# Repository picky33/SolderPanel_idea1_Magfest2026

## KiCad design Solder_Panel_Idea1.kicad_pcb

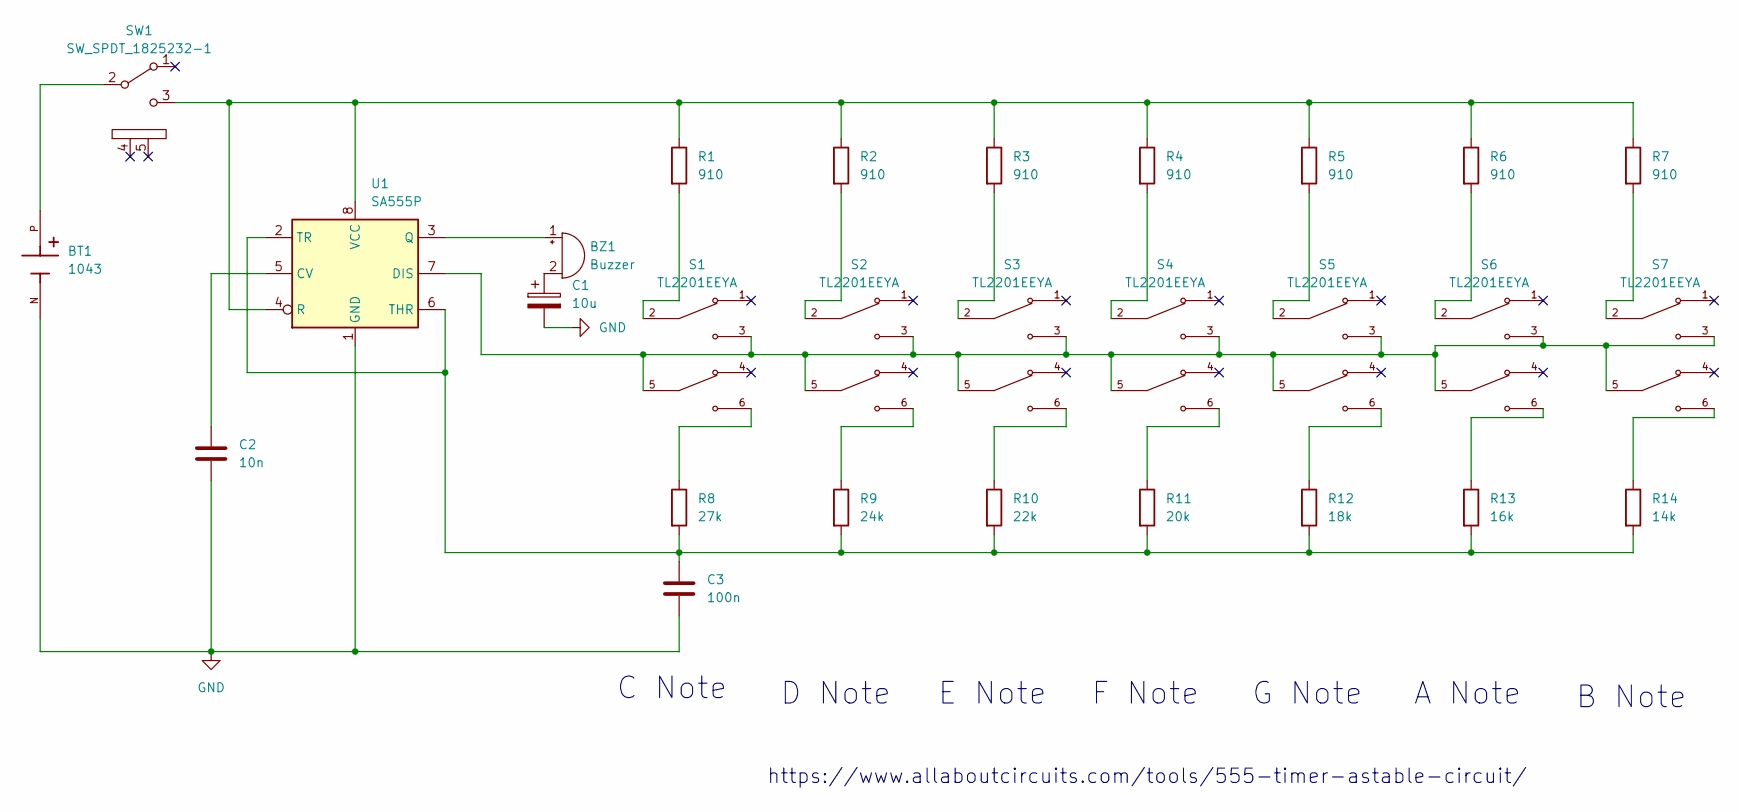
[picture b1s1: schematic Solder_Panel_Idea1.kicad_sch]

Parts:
BT1: 1043; BAT_1043; PARTREV J
BZ1: Buzzer; Buzzer_12.5x7.5; Digikey 433-1285-ND
C1: 10u; C_Radial_D5.0mm_H7.0mm_P2.00mm
C2: 10n; C_Disc_D7.5mm_W2.5mm_P5.00mm
C3: 100n; C_Disc_D7.5mm_W2.5mm_P5.00mm
R1, R2, R3, R4, R5, R6, R7: 910; R_Axial_DIN0411_L9.9mm_D3.6mm_P15.24mm_Horizontal
R8: 27k; R_Axial_DIN0411_L9.9mm_D3.6mm_P15.24mm_Horizontal
R9: 24k; R_Axial_DIN0411_L9.9mm_D3.6mm_P15.24mm_Horizontal
R10: 22k; R_Axial_DIN0411_L9.9mm_D3.6mm_P15.24mm_Horizontal
R11: 20k; R_Axial_DIN0411_L9.9mm_D3.6mm_P15.24mm_Horizontal
R12: 18k; R_Axial_DIN0411_L9.9mm_D3.6mm_P15.24mm_Horizontal
R13: 16k; R_Axial_DIN0411_L9.9mm_D3.6mm_P15.24mm_Horizontal
R14: 14k; R_Axial_DIN0411_L9.9mm_D3.6mm_P15.24mm_Horizontal
S1, S2, S3, S4, S5, S6, S7: TL2201EEYA; SW_TL2201EEYA
SW1: SW_SPDT_1825232-1; 1825232-1; Digikey A107673-ND
U1: SA555P; DIP-8_W7.62mm_LongPads

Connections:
GND: BT1.N, C1.2, C2.2, C3.2, U1.1 (GND)
unnamed: BZ1.2 (+), C1.1
unnamed: BZ1.1 (-), U1.3 (Q)
unnamed: R1.2, S1.2
unnamed: R2.2, S2.2
unnamed: R3.2, S3.2
unnamed: R4.2, S4.2
unnamed: R5.2, S5.2
unnamed: R6.2, S6.2
unnamed: R7.2, S7.2
unnamed: R8.1, S1.6
unnamed: R9.1, S2.6
unnamed: R10.1, S3.6
unnamed: R11.1, S4.6
unnamed: R12.1, S5.6
unnamed: R13.1, S6.6
unnamed: R14.1, S7.6
unnamed: BT1.P, SW1.2 (B)
unnamed: R1.1, R2.1, R3.1, R4.1, R5.1, R6.1, R7.1, SW1.3 (C), U1.4 (R), U1.8 (VCC)
unnamed: C2.1, U1.5 (CV)
unnamed: S1.3, S1.5, S2.3, S2.5, S3.3, S3.5, S4.3, S4.5, S5.3, S5.5, S6.3, S6.5, S7.3, S7.5, U1.7 (DIS)
unnamed: C3.1, R8.2, R9.2, R10.2, R11.2, R12.2, R13.2, R14.2, U1.2 (TR), U1.6 (THR)

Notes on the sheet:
C Note
G Note
F Note
E Note
https://www.allaboutcircuits.com/tools/555-timer-astable-circuit/
A Note
B Note
D Note

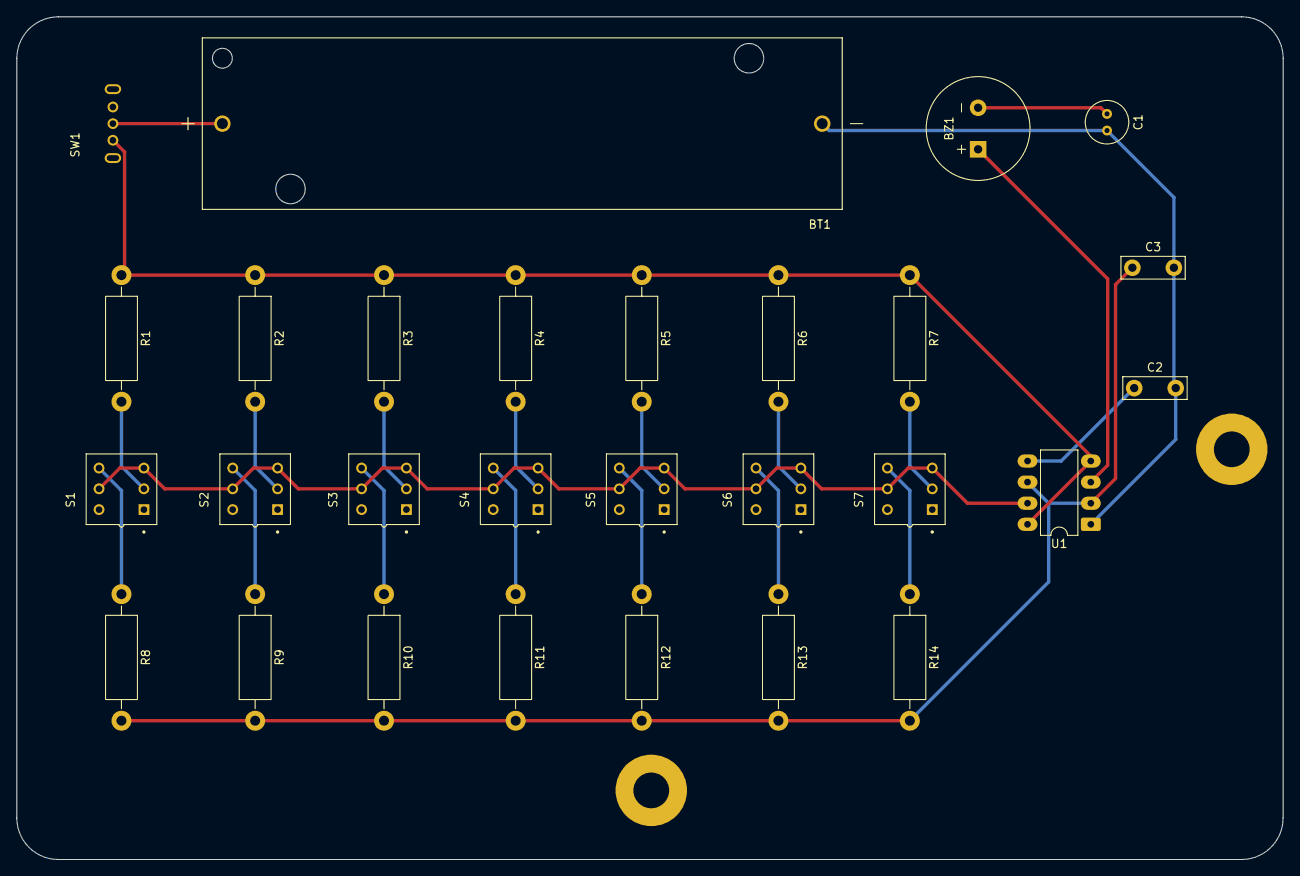
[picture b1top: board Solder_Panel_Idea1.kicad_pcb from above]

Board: 2 copper layers, 152.5 x 101.5 mm, 28 parts (0 on the bottom side), 22 nets.

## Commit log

2025-10-14 Initial Upload
2025-10-15 Uploaded the Real File
    the last set of files was wrong directory
2025-10-15 hopefully correcting Git
2025-10-15 Should be good now
    Hopefully
2025-10-15 Added Holes
